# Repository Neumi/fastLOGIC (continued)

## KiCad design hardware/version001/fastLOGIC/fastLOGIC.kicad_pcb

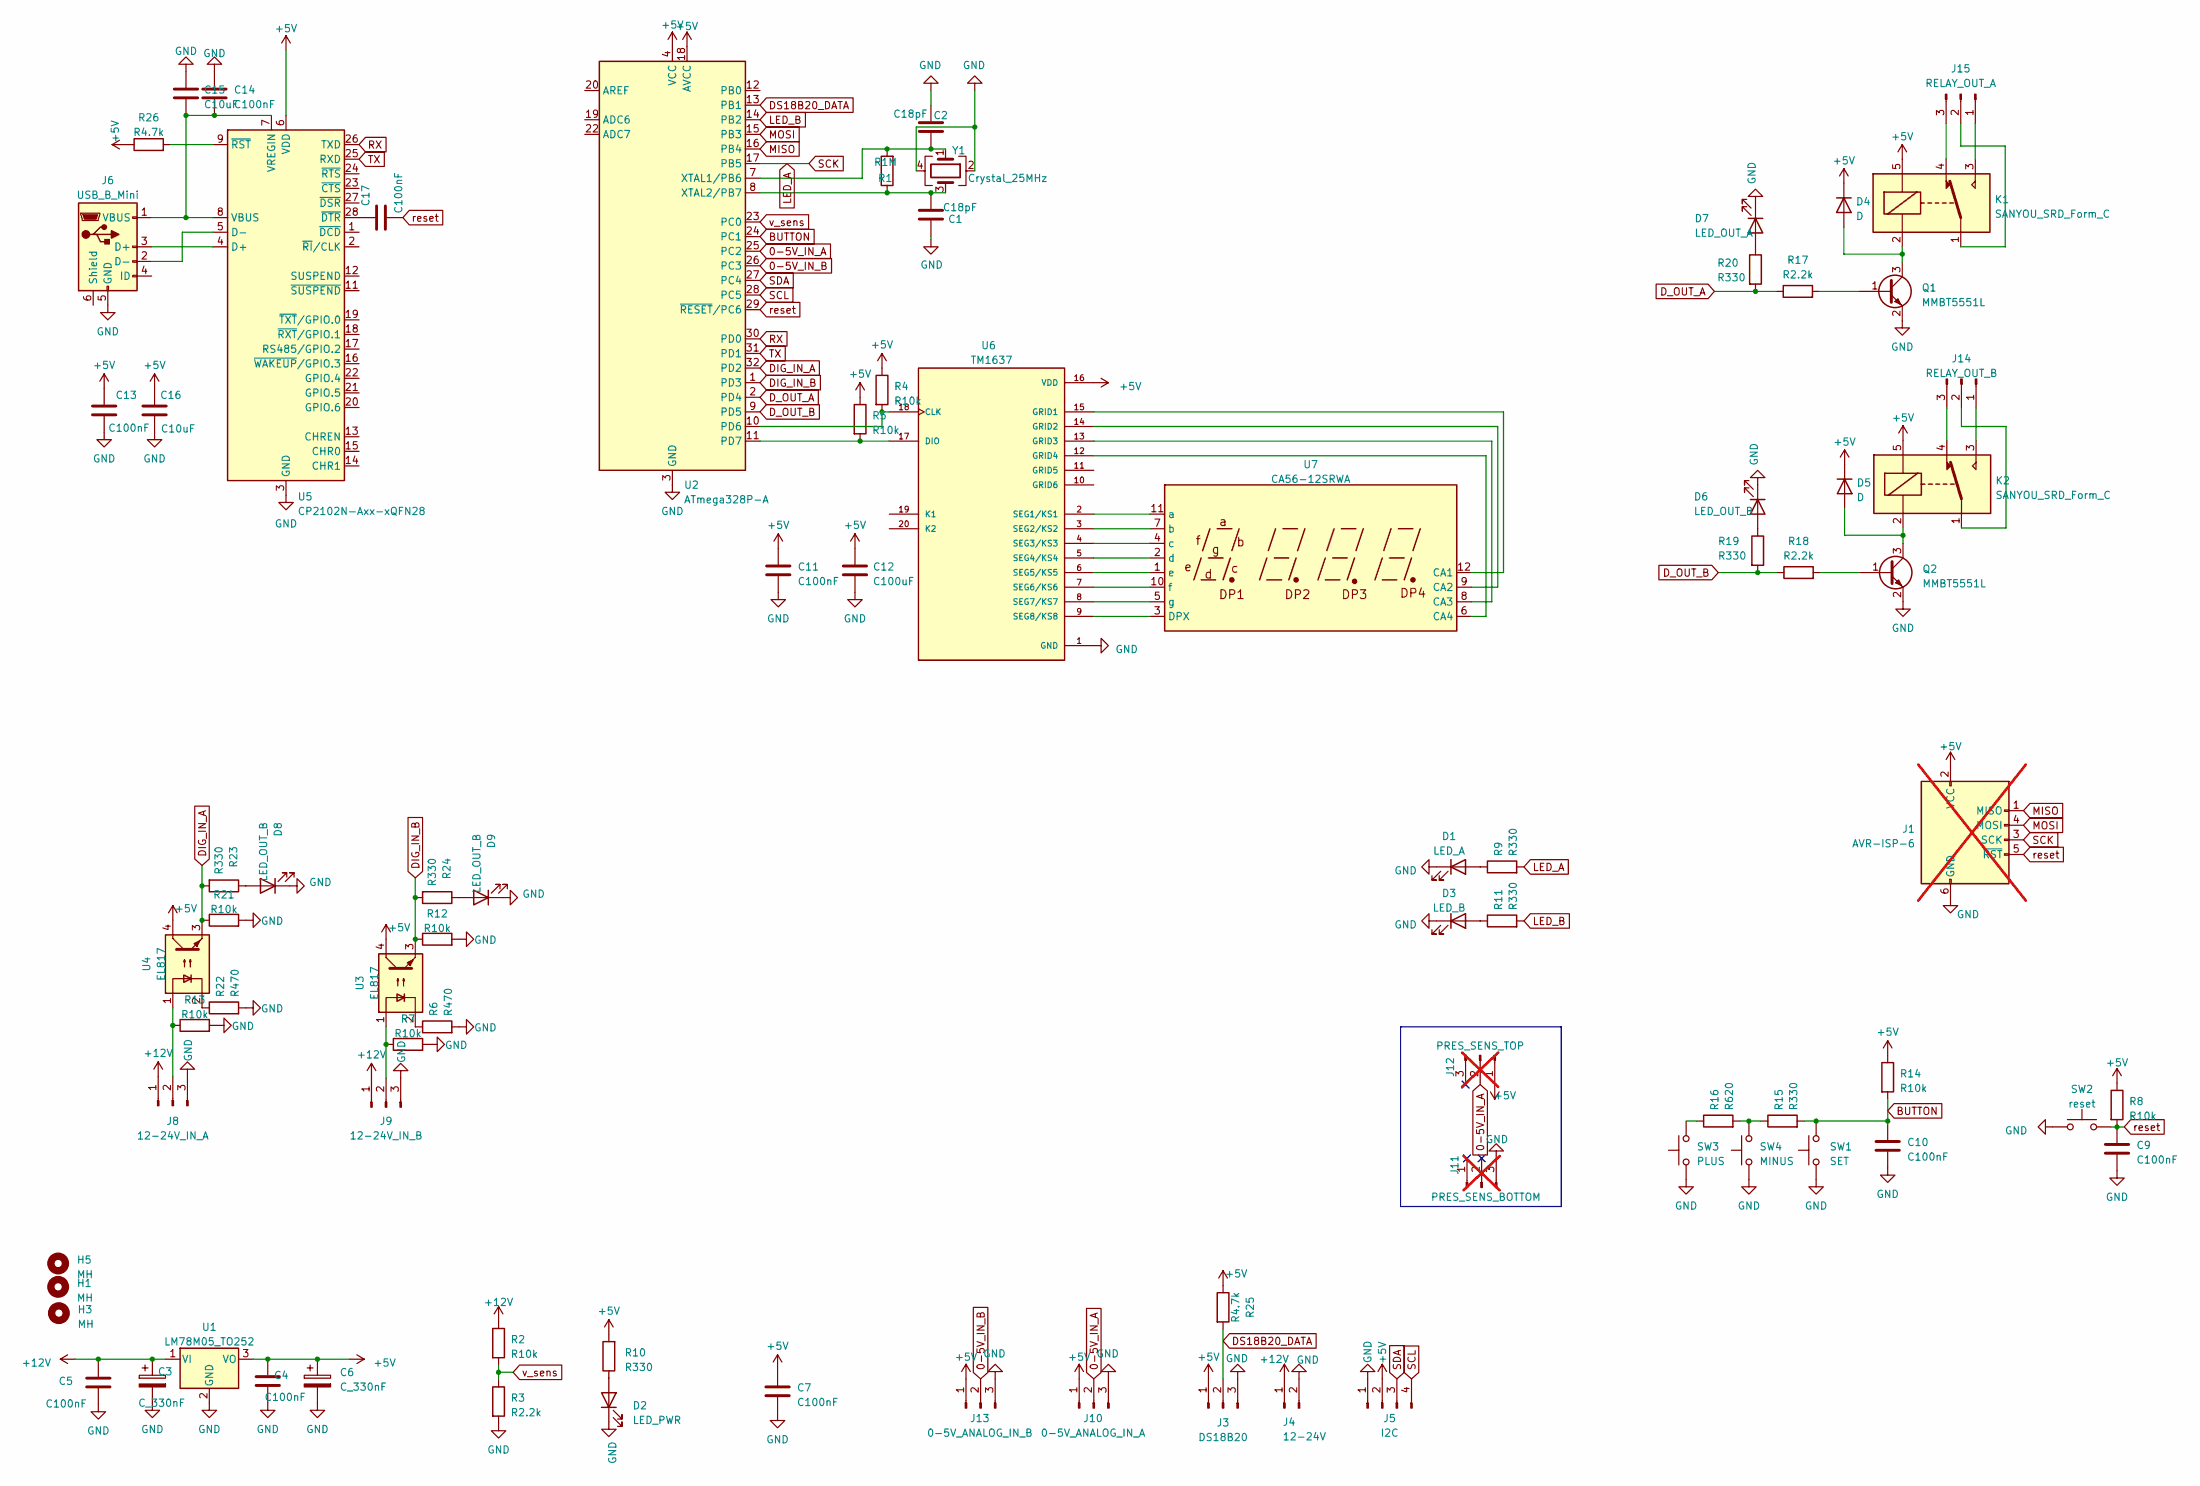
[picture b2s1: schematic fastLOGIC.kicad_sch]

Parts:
C1, C2: C18pF; C_0402_1005Metric; LCSC C1549
C3, C6: C_330nF; CP_Elec_4x5.4; LCSC C264238
C4, C5: C100nF; C_1206_3216Metric; LCSC C24497
C7, C9, C10, C11, C13, C14, C17: C100nF; C_0603_1608Metric; LCSC C14663
C12: C100uF; C_1206_3216Metric; LCSC C15008
C15, C16: C10uF; C_0805_2012Metric; LCSC C15850
D1: LED_A; LED_0805_2012Metric; LCSC C2296
D2: LED_PWR; LED_0805_2012Metric; LCSC C84256
D3: LED_B; LED_0805_2012Metric; LCSC C2296
D4, D5: D; D_SMA; LCSC C22452
D6, D8, D9: LED_OUT_B; LED_0805_2012Metric; LCSC C2296
D7: LED_OUT_A; LED_0805_2012Metric; LCSC C2296
H1, H3, H5: MH; MountingHole_3.2mm_M3_DIN965
J1: AVR-ISP-6; IDC-Header_2x03_P2.54mm_Vertical; not fitted
J3: DS18B20; JST_EH_S3B-EH_1x03_P2.50mm_Horizontal; LCSC C157928
J4: 12-24V; TerminalBlock_4Ucon_1x02_P3.50mm_Vertical; LCSC C2997509
J5: I2C; JST_EH_S4B-EH_1x04_P2.50mm_Horizontal; LCSC C157925
J6: USB_B_Mini; USB_Mini-B_Tensility_54-00023_Vertical; LCSC C6331167
J8: 12-24V_IN_A; TerminalBlock_4Ucon_1x03_P3.50mm_Vertical; LCSC C2997510
J9: 12-24V_IN_B; TerminalBlock_4Ucon_1x03_P3.50mm_Vertical; LCSC C2997510
J10: 0-5V_ANALOG_IN_A; JST_EH_S3B-EH_1x03_P2.50mm_Horizontal; LCSC C157928
J11: PRES_SENS_BOTTOM; PinHeader_1x03_P2.54mm_Vertical; not fitted
J12: PRES_SENS_TOP; PinHeader_1x03_P2.54mm_Vertical; not fitted
J13: 0-5V_ANALOG_IN_B; JST_EH_S3B-EH_1x03_P2.50mm_Horizontal; LCSC C157928
J14: RELAY_OUT_B; TerminalBlock_4Ucon_1x03_P3.50mm_Vertical; LCSC C2997510
J15: RELAY_OUT_A; TerminalBlock_4Ucon_1x03_P3.50mm_Vertical; LCSC C2997510
K1, K2: SANYOU_SRD_Form_C; Relay_SPDT_SANYOU_SRD_Series_Form_C; LCSC C35449
Q1, Q2: MMBT5551L; SOT-23; LCSC C2145
R1: R1M; R_0603_1608Metric; LCSC C22935
R2, R4, R5, R7, R8, R12, R13, R14, R21: R10k; R_0603_1608Metric; LCSC C25804
R3, R17, R18: R2.2k; R_0603_1608Metric; LCSC C4190
R6, R22: R470; R_0603_1608Metric; LCSC C23179
R9, R10, R11, R15, R19, R20, R23, R24: R330; R_0603_1608Metric; LCSC C23138
R16: R620; R_0603_1608Metric; LCSC C4260
R25, R26: R4.7k; R_0603_1608Metric; LCSC C23162
SW1: SET; SW_Push_1P1T_NO_CK_KSC7xxJ; LCSC C318884
SW2: reset; SW_Push_1P1T_NO_CK_KSC7xxJ; LCSC C318884
SW3: PLUS; SW_Push_1P1T_NO_CK_KSC7xxJ; LCSC C318884
SW4: MINUS; SW_Push_1P1T_NO_CK_KSC7xxJ; LCSC C318884
U1: LM78M05_TO252; TO-252-2; LCSC C58069
U2: ATmega328P-A; TQFP-32_7x7mm_P0.8mm
U3, U4: EL817; DIP-4_W8.89mm_SMDSocket_LongPads; LCSC C106900
U5: CP2102N-Axx-xQFN28; QFN-28-1EP_5x5mm_P0.5mm_EP3.35x3.35mm; LCSC C6568
U6: TM1637; SOP-20_7.5x12.8mm_P1.27mm; PARTREV v2.5; LCSC C2962580
U7: CA56-12SRWA; LCSC C38183
Y1: Crystal_25MHz; Crystal_SMD_3225-4Pin_3.2x2.5mm; LCSC C13738

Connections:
0-5V_IN_A: J10.2, J12.2, U2.25 (PC2)
0-5V_IN_B: J13.2, U2.26 (PC3)
+5V: C4.1, C6.1, C7.1, C11.1, C12.1, C13.1, C16.1, D4.1 (K), D5.1 (K), J1.2 (VCC), J3.1, J5.2, J10.1, J12.1, J13.1, K1.5, K2.5, R4.1, R5.1, R8.1, R10.2, R14.1, R25.1, R26.1, U1.3 (VO), U2.4 (VCC), U2.6 (VCC), U2.18 (AVCC), U3.4, U4.4, U5.6 (VDD), U6.16 (VDD)
+12V: C3.1, C5.1, J4.1, J8.1, J9.1, R2.1, U1.1 (VI)
BUTTON: C10.1, R14.2, R15.2, SW1.2, U2.24 (PC1)
DIG_IN_A: R21.1, R23.2, U2.32 (PD2), U4.3
DIG_IN_B: R12.1, R24.2, U2.1 (PD3), U3.3
DS18B20_DATA: J3.2, R25.2, U2.13 (PB1)
D_OUT_A: R17.1, R20.2, U2.2 (PD4)
D_OUT_B: R18.1, R19.2, U2.9 (PD5)
GND: C1.1, C2.2, C3.2, C4.2, C5.2, C6.2, C7.2, C9.2, C10.2, C11.2, C12.2, C13.2, C14.1, C15.1, C16.2, D1.1 (K), D2.1 (K), D3.1 (K), D6.1 (K), D7.1 (K), D8.1 (K), D9.1 (K), J1.6 (GND), J3.3, J4.2, J5.1, J6.5 (GND), J8.3, J9.3, J10.3, J11.3, J13.3, Q1.2 (E), Q2.2 (E), R3.2, R6.2, R7.2, R12.2, R13.2, R21.2, R22.2, SW1.1, SW2.1, SW3.1, SW4.1, U1.2 (GND), U2.3 (GND), U2.5 (GND), U2.21 (GND), U5.3 (GND), U5.29 (GND), U6.1 (GND), Y1.2, Y1.4
LED_A: J1.3 (SCK), R9.2, U2.17 (PB5)
LED_B: R11.2, U2.14 (PB2)
MISO: J1.1 (MISO), U2.16 (PB4)
MOSI: J1.4 (MOSI), U2.15 (PB3)
unnamed: D1.2 (A), R9.1
unnamed: D2.2 (A), R10.1
unnamed: D3.2 (A), R11.1
unnamed: D4.2 (A), K1.2, Q1.3 (C)
unnamed: D5.2 (A), K2.2, Q2.3 (C)
unnamed: D6.2 (A), R19.1
unnamed: D7.2 (A), R20.1
unnamed: D8.2 (A), R23.1
unnamed: D9.2 (A), R24.1
unnamed: J6.3 (D+), U5.4 (D+)
unnamed: J6.2 (D-), U5.5 (D-)
unnamed: C14.2, C15.2, J6.1 (VBUS), U5.7 (VREGIN), U5.8 (VBUS)
unnamed: J8.2, R13.1, U4.1
unnamed: J9.2, R7.1, U3.1
unnamed: J14.1, K2.3
unnamed: J14.2, K2.1
unnamed: J14.3, K2.4
unnamed: J15.1, K1.3
unnamed: J15.2, K1.1
unnamed: J15.3, K1.4
unnamed: Q1.1 (B), R17.2
unnamed: Q2.1 (B), R18.2
unnamed: R6.1, U3.2
unnamed: R15.1, R16.2, SW4.2
unnamed: R16.1, SW3.2
unnamed: R22.1, U4.2
unnamed: R4.2, U2.10 (PD6), U6.18 (CLK)
unnamed: R5.2, U2.11 (PD7), U6.17 (DIO)
unnamed: C2.1, R1.2, U2.7 (XTAL1/PB6), Y1.1
unnamed: C1.2, R1.1, U2.8 (XTAL2/PB7), Y1.3
unnamed: C17.1, U5.28 (~DTR)
unnamed: R26.2, U5.9 (~RST)
unnamed: U6.15 (GRID1), U7.12 (CA1)
unnamed: U6.14 (GRID2), U7.9 (CA2)
unnamed: U6.13 (GRID3), U7.8 (CA3)
unnamed: U6.12 (GRID4), U7.6 (CA4)
unnamed: U6.2 (SEG1/KS1), U7.11 (a)
unnamed: U6.3 (SEG2/KS2), U7.7 (b)
unnamed: U6.4 (SEG3/KS3), U7.4 (c)
unnamed: U6.5 (SEG4/KS4), U7.2 (d)
unnamed: U6.6 (SEG5/KS5), U7.1 (e)
unnamed: U6.7 (SEG6/KS6), U7.10 (f)
unnamed: U6.8 (SEG7/KS7), U7.5 (g)
unnamed: U6.9 (SEG8/KS8), U7.3 (DPX)
RX: U2.30 (PD0), U5.26 (TXD)
SCL: J5.4, U2.28 (PC5)
SDA: J5.3, U2.27 (PC4)
TX: U2.31 (PD1), U5.25 (RXD)
reset: C9.1, C17.2, J1.5 (~RST), R8.2, SW2.2, U2.29 (~RESET/PC6)
v_sens: R2.2, R3.1, U2.23 (PC0)

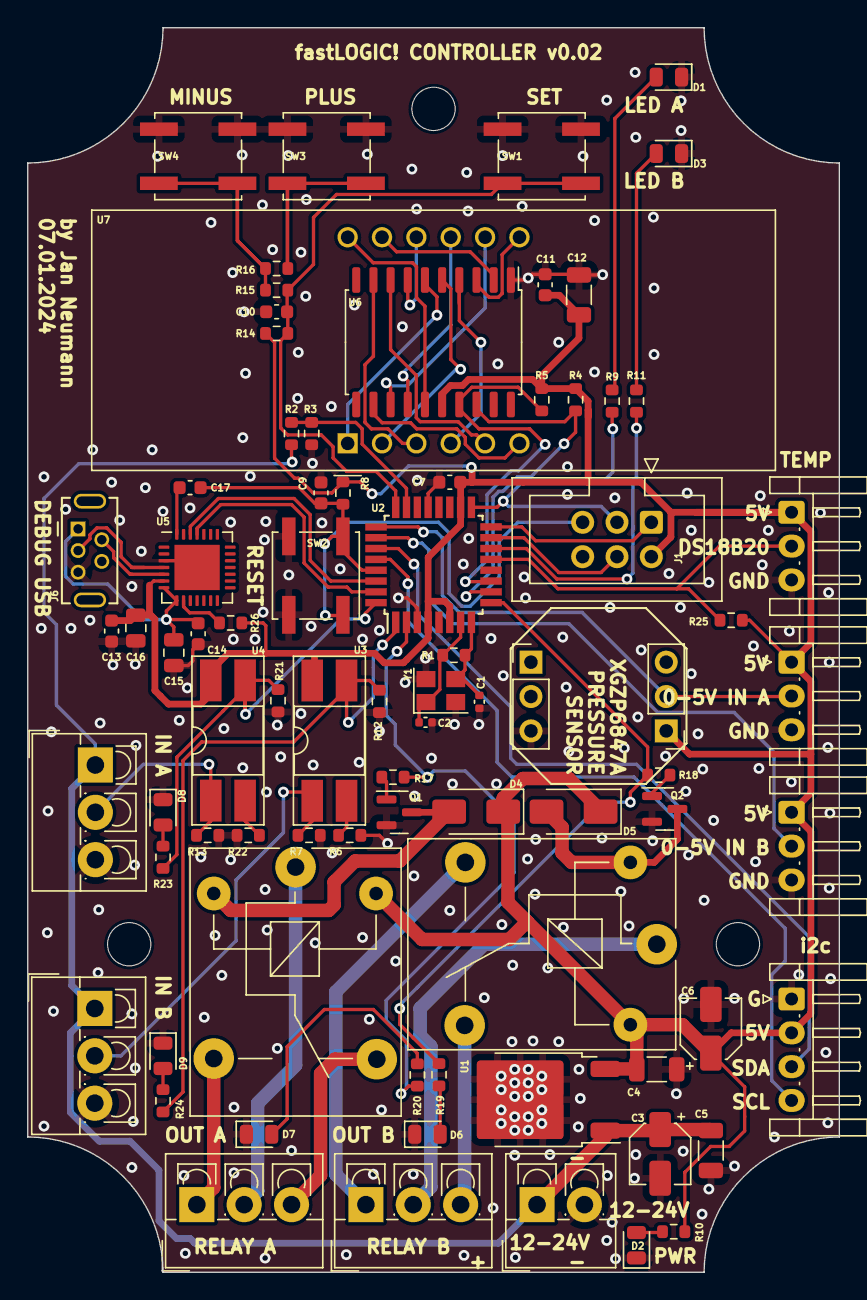
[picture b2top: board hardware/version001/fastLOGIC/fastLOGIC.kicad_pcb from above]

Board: 2 copper layers, 60.0 x 92.0 mm, 83 parts (0 on the bottom side), 65 nets.

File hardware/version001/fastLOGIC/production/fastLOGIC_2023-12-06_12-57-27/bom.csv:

Designator,Footprint,Quantity,Value,LCSC Part #
"C1, C2",0402,2,C18pF,C1549
"C10, C11, C13, C14, C17, C7, C9",0603,7,C100nF,C14663
C12,1206,1,C100uF,C15008
"C15, C16",0805,2,C10uF,C15850
"C3, C6",CP_Elec_4x5.4,2,C_330nF,C264238
"C4, C5",1206,2,C100nF,C24497
D1,0805,1,LED_A,C2296
D2,0805,1,LED_PWR,C84256
D3,0805,1,LED_B,C2296
"D4, D5",D_SMA,2,D,C22452
"D6, D8, D9",0805,3,LED_OUT_B,C2296
D7,0805,1,LED_OUT_A,C2296
"H1, H3, H5",MountingHole_3.2mm_M3_DIN965,3,MH,
J10,JST_EH_S3B-EH_1x03_P2.50mm_Horizontal,1,0-5V_ANALOG_IN_A,
J13,JST_EH_S3B-EH_1x03_P2.50mm_Horizontal,1,0-5V_ANALOG_IN_B,
J14,TerminalBlock_4Ucon_1x03_P3.50mm_Vertical,1,RELAY_OUT_B,
J15,TerminalBlock_4Ucon_1x03_P3.50mm_Vertical,1,RELAY_OUT_A,
J2,USB_Micro-B_Amphenol_10118194_Horizontal,1,USB_B_Micro,
J3,JST_EH_S3B-EH_1x03_P2.50mm_Horizontal,1,DS18B20,
J4,TerminalBlock_4Ucon_1x02_P3.50mm_Vertical,1,12-24V,
J5,JST_EH_S4B-EH_1x04_P2.50mm_Horizontal,1,I2C,
J8,TerminalBlock_4Ucon_1x03_P3.50mm_Vertical,1,12-24V_IN_A,
J9,TerminalBlock_4Ucon_1x03_P3.50mm_Vertical,1,12-24V_IN_B,
"K1, K2",Relay_SPDT_SANYOU_SRD_Series_Form_C,2,SANYOU_SRD_Form_C,C35449
"Q1, Q2",SOT-23,2,MMBT5551L,C2145
R1,0603,1,R1M,C22935
"R10, R11, R15, R19, R20, R23, R24, R9",0603,8,R330,C23138
"R12, R13, R14, R2, R21, R4, R5, R7, R8",0603,9,R10k,C25804
R16,0603,1,R620,C4260
"R17, R18, R3",0603,3,R2.2k,C4190
"R22, R6",0603,2,R470,C23179
R25,0603,1,R4.7k,C23162
SW1,SW_Push_1P1T_NO_CK_KSC7xxJ,1,SET,C318884
SW2,SW_Push_1P1T_NO_CK_KSC7xxJ,1,reset,C318884
SW3,SW_Push_1P1T_NO_CK_KSC7xxJ,1,PLUS,C318884
SW4,SW_Push_1P1T_NO_CK_KSC7xxJ,1,MINUS,C318884
U1,TO-252-2,1,LM78M05_TO252,C58069
U2,TQFP-32_7x7mm_P0.8mm,1,ATmega328P-A,
"U3, U4",DIP-4_W7.62mm_SMDSocket_SmallPads,2,EL817,C106900
U5,QFN-28-1EP_5x5mm_P0.5mm_EP3.35x3.35mm,1,CP2102N-Axx-xQFN28,C6568
U6,SOP-20_7.5x12.8mm_P1.27mm,1,TM1637,C2962580
U7,CA56-12SRWA,1,CA56-12SRWA,
Y1,Crystal_SMD_3225-4Pin_3.2x2.5mm,1,Crystal_25MHz,C13738

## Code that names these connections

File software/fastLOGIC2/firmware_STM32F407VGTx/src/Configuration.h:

#pragma once

const String version = "0.21"; // software version

#define STATIC_IP 0 // when set 1, DHCP is enabled, when 0, statis IP is used

#define DEBUG_MODE 1 // when set 1, debugging output is enabled

#define BAUD_SPEED 9600 // debug and message baud speed

#define SYS_VOL 3.3 // system voltage in volts

#define BUFFER_SIZE 256 // communication buffer size

#define LOCAL_PORT 8888 // local UDP port

#define STANDARD_REMOTE_SENSOR_PORT 5000 // remote machines receiving UDP port

#define DEFAULT_DISPLAY_REFRESH_TIME 100 // milliseconds until new data is shown
#define DEFAULT_FEEDBACK_TIME 100 // milliseconds until hearbeat


// scheduler modes
#define standby 0 // waiting for instructions
#define running 1 // running drive loop

// connection modes
#define CONNECTION_STAT "STAT"
#define CONNECTION_DHCP "DHCP"
#define CONNECTION_USB "USB "
 

// I/O
#define LED_PIN PC13

#define LCD_BG_LED_PIN PE9
#define LCD_SI PE10
#define LCD_SCL PE11    
#define LCD_RS PE12
#define LCD_RSE PE13
#define LCD_CS PE14

#define SD_DET PE15
#define SD_CMD PD2
#define SD_D0 PC8
#define SD_D1 PC9
#define SD_D2 PC10
#define SD_D3 PC11
#define SD_CLK PC12

#define MAX485_DI PC6
#define MAX485_RO PC7
#define MAX485_RE PD14
#define MAX485_DE PD15

#define ETHERNET_INT PA3
#define ETHERNET_RST PA2
#define ETHERNET_CS PA1
#define ETHERNET_MISO PA6
#define ETHERNET_MOSI PA7
#define ETHERNET_SCK PA5

#define DS18B20_PIN PD12

#define TX1 PA9
#define RX1 PA10
#define TX2 PD5
#define RX2 PD6

#define SCL1 PB6
#define SDA1 PB7
#define SCL2 PB10
#define SDA2 PB11

#define LEDA PB15
#define LEDB PB14
#define LEDC PB13
#define LEDD PB12

#define DIGITAL_IN_A PE7
#define DIGITAL_IN_B PE8

#define RELAY_OUT_A PD0
#define RELAY_OUT_B PD1
#define RELAY_OUT_C PD3

#define BUTTON_SET_IN PD4
#define BUTTON_PLUS_IN PD7
#define BUTTON_MINUS_IN PB3

#define VOLT_DETECT_PIN_5V PE0 // false pinmap NOT SUITABLE FOR ADC VOLTAGE MEASUREMENT
#define VOLT_DETECT_PIN_VIN PB0

#define ANALOG_IN_A PC5
#define ANALOG_IN_B PC4

#define PRESSURE_SENSOR_PIN PE1 // false pinmap NOT SUITABLE FOR ADC PRESSURE MEASUREMENT

#define CURRENT_SENSE_PIN_A PC2
#define CURRENT_SENSE_PIN_B PC1
#define CURRENT_SENSE_PIN_C PC0

#define UC_TX PA9
#define UC_RX PA10

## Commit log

2023-12-06 initial hardware and images
2023-12-06 layout changes, mini usb connector, case with lid 3d, minor stuff
2023-12-06 added assembly image
2023-12-06 changed images
2023-12-06 added
2023-12-06 removed old production files
2023-12-06 hardware chnages minor
2023-12-06 cleanup
2023-12-06 Update README.md
    added description image
2023-12-06 added production folder of JLC order
2023-12-06 removed old production
2023-12-06 latest pcb
2023-12-30 changed holes, vias and markings
2023-12-30 added images
2024-01-04 minor pcb changes, image
2024-01-04 added library and example arduino firmware
2024-01-04 changed keywords file
2024-01-04 changed description image, added relay 2 output
2024-01-06 Added Pull Up Resistor on CP2102 RST Pin
    As per the datasheet Typical Connection Diagrams, a 1kΩ pull-up on the RST is recommended
2024-02-08 hardware minor mistake fixes
2024-02-08 Update README.md
    added more description
2024-02-16 Implementation of i2c to rs485 on the software side
2024-02-16 Implementation of the i2c to rs485 class
2024-02-16 Method implementation of scanI2CBus
2024-02-16 Method implementation of readDataFromI2C
2024-02-16 Changed german commentary to english
2024-02-16 Implementation RS485 DE/RE Control
2024-02-16 Added commentary and changed print out from german to english
2024-02-16 [Fix] Moved definitions to header file
2024-02-21 Added TM1637Display class and header file to library
2024-03-03 Revert "Added TM1637Display class and header file to library"
    This reverts commit 9c375d7bc24ca8d8b0535c5665fffe9af0f2e29c.
2024-03-03 Adding settingsMenu class and header with basic functionality for 7-segment displays and buttons
2024-03-17 [Refactor] Relocate settingsMenu to library
2024-03-17 Implementation of handleMenuNavigation and updateDisplay with basic functionality
2024-03-17 Rework code for updateDisplay and handleMenuNavigation to work with baud and rs485
2024-03-17 Added showText for delayed display at one display. could be used for a marquee loop
2024-03-17 Split showText into showTextLoop and showText to display one word across 4 displays
2024-03-17 [Gitignore] Add .vscode properties
2024-03-26 added ignore
2024-04-09 improved schematic overview with more data added
2024-04-09 chnaged pinout on description image
2024-04-15 fixed relay pin mapping and added SPI connector
2024-04-15 added documentation pdf
2024-04-18 adde led shine on description img
2024-07-12 none
2024-07-12 adde ignor
2024-09-03 added HW version 002, incl 3d files, PCB design
2024-12-31 hardware version 2.0 finished and sent to manufacturer
2025-03-31 heap commit, not up to date changes. rest following
2025-05-05 added sponsoring
